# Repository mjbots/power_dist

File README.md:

# mjbots power_dist and mjpower-ss #

This repository contains hardware and firmware for the mjbots
power_dist and mjpower-ss boards.  Both provide pre-charge,
over-current limiting and connector fanout.  The power_dist
additionally provides energy monitoring and a soft-switch
functionality.

# Specifications #

| Name                     | power_dist r4.5b | mjpower-ss r2 |
| ------------------------ |------------------|---------------|
| Voltage Input            | 10-44V           | 10-54V        |
| Current (continous/peak) | 45A/90A          | 45/90A        |
| Output                   | 6x XT30          | 6x XT30       |
| Max load capacitance     | 4000uF           | 4000uF        |
| Quiescent current        | 300uA            | 200uA         |
| Dimensions               | 80x50mm          | 70x50mm       |
| Mass                     | 36g              | 34g           |
| External switch          | X                | X             |
| Soft switch              | X                |               |
| Onboard switch           |                  | X             |
| CAN communication        | X                |               |

# Documentation #

* [Reference](docs/reference.md)

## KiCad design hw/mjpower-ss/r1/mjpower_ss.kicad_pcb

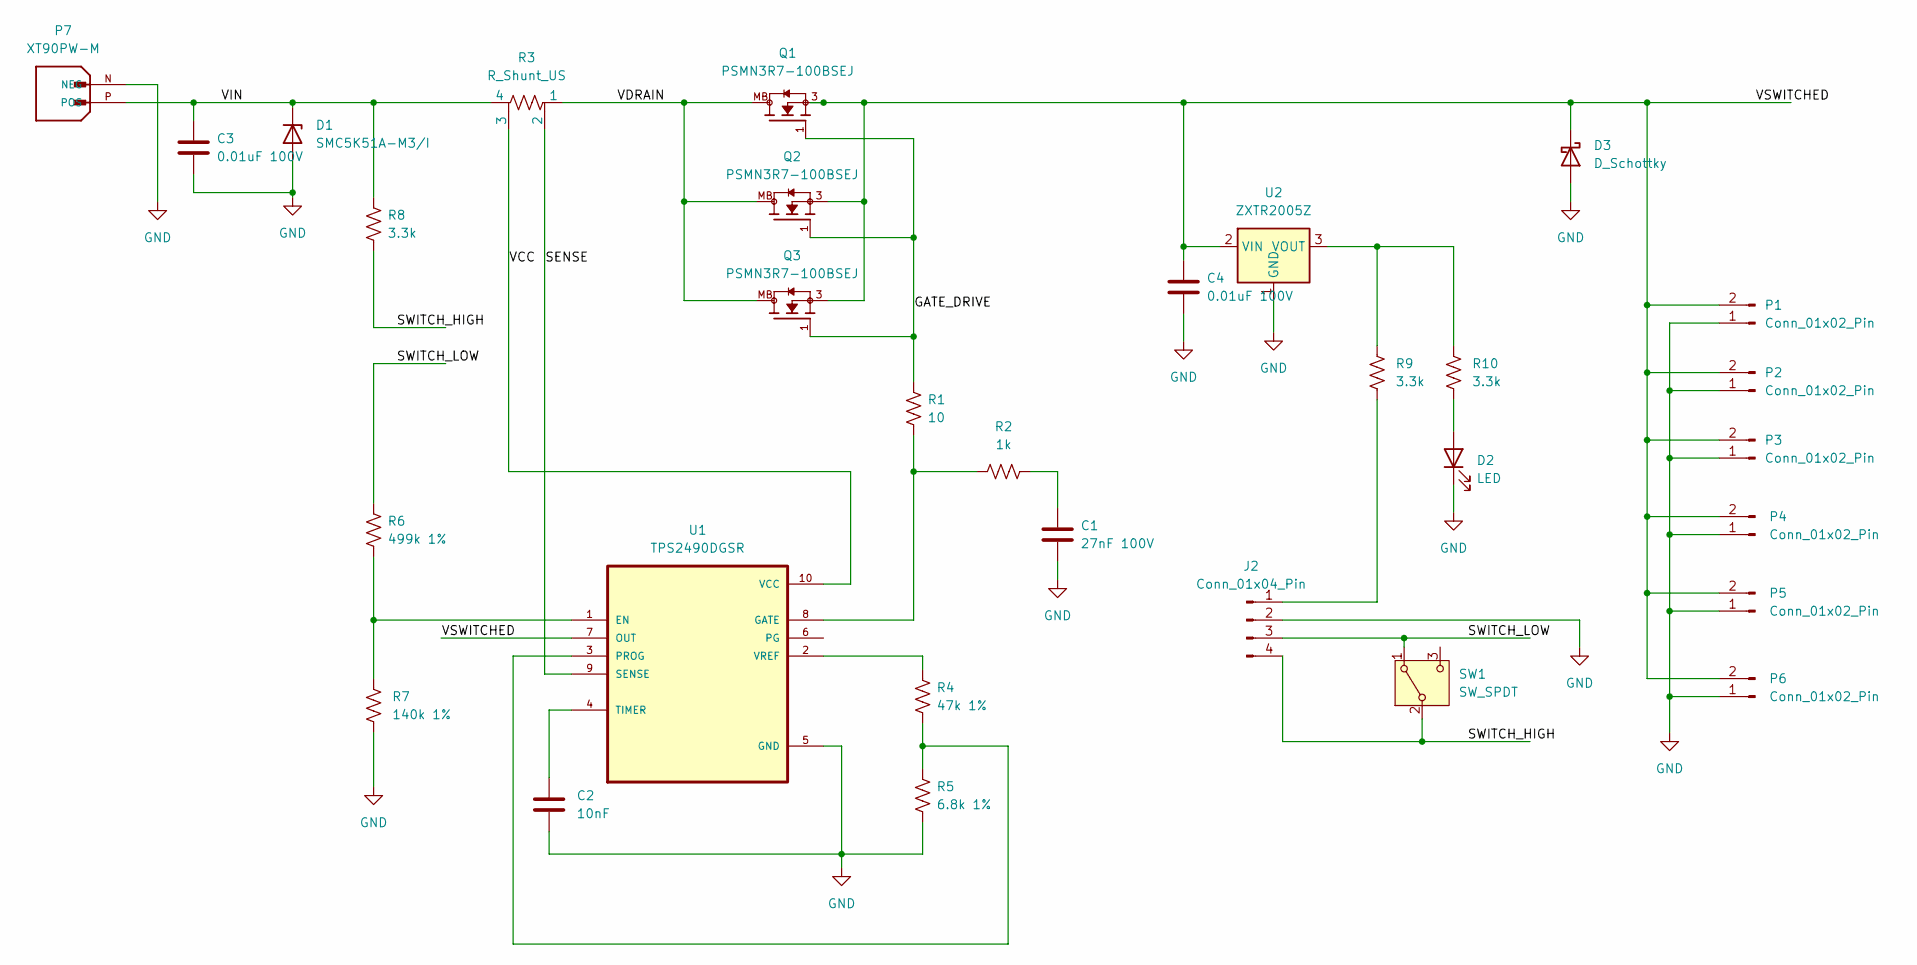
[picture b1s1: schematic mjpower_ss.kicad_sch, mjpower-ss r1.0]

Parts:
C1: 27nF 100V; C_0603_1608Metric; MPN C0603C273K1RACTU
C2: 10nF; C_0603_1608Metric; MPN MF-CAP-0603-0.01uF
C3, C4: 0.01uF 100V; C_0603_1608Metric; MPN GCM188R72A103KA37D
D1: SMC5K51A-M3/I; D_SMC; MPN SMC5K51A-M3/I
D2: LED; LED_1210_3225Metric; MPN APD3224ZGC-F01
D3: D_Schottky; TO-277A; MPN V10P15-M3/H
J2: Conn_01x04_Pin; JST_B4B-PH-SM4-TB; MPN B4B-PH-SM4-TB(LF)(SN)
P1, P2, P3, P4, P5, P6: Conn_01x02_Pin; XT30UPB-F; MPN XT30UPB-F
P7: XT90PW-M; AMASS_XT90PW-M; MPN XT90PW-M
Q1, Q2, Q3: PSMN3R7-100BSEJ; TRANS_PSMN3R7-100BSEJ; MPN PSMN3R7-100BSEJ
R1: 10; R_0603_1608Metric; MPN MF-RES-0603-10
R2: 1k; R_0603_1608Metric; MPN MF-RES-0603-1K
R3: R_Shunt_US; WSL2512_SHUNT; MPN WSLF2512L5000FEA
R4: 47k 1%; R_0603_1608Metric; MPN RC0603FR-0747KL
R5: 6.8k 1%; R_0603_1608Metric; MPN RC0603FR-076K8L
R6: 499k 1%; R_0603_1608Metric; MPN RC0603FR-07499KL
R7: 140k 1%; R_0603_1608Metric; MPN RC0603FR-07140KL
R8, R9, R10: 3.3k; R_0603_1608Metric; MPN RC0603FR-073K3L
SW1: SW_SPDT; SW_G-107-0513; MPN G-107-0513
U1: TPS2490DGSR; SOP50P490X110-10N; MPN TPS2490DGSR
U2: ZXTR2005Z; SOT-89-3; MPN ZXTR2005Z-13

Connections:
/GATE_DRIVE: Q1.1, Q2.1, Q3.1, R1.1
/SENSE: R3.2, U1.9 (SENSE)
/SWITCH_HIGH: J2.4, R8.2, SW1.2 (B)
/SWITCH_LOW: J2.3, R6.1, SW1.1 (A)
/VCC: R3.3, U1.10 (VCC)
/VDRAIN: Q1.MB, Q2.MB, Q3.MB, R3.1
/VIN: C3.1, D1.1 (K), P7.P (POS), R3.4, R8.1
/VSWITCHED: C4.1, D3.1 (K), P1.2, P2.2, P3.2, P4.2, P5.2, P6.2, Q1.3, Q2.3, Q3.3, U1.7 (OUT), U2.2 (VIN)
GND: C1.2, C2.2, C3.2, C4.2, D1.2 (A), D2.1 (K), D3.2 (A), J2.2, P1.1, P2.1, P3.1, P4.1, P5.1, P6.1, P7.N (NEG), R5.2, R7.2, U1.5 (GND), U2.1 (GND)
unnamed: C1.1, R2.2
unnamed: D2.2 (A), R10.1
unnamed: J2.1, R9.1
unnamed: R6.2, R7.1, U1.1 (EN)
unnamed: R1.2, R2.1, U1.8 (GATE)
unnamed: R4.2, R5.1, U1.3 (PROG)
unnamed: C2.1, U1.4 (TIMER)
unnamed: R4.1, U1.2 (VREF)
unnamed: R9.2, R10.2, U2.3 (VOUT)

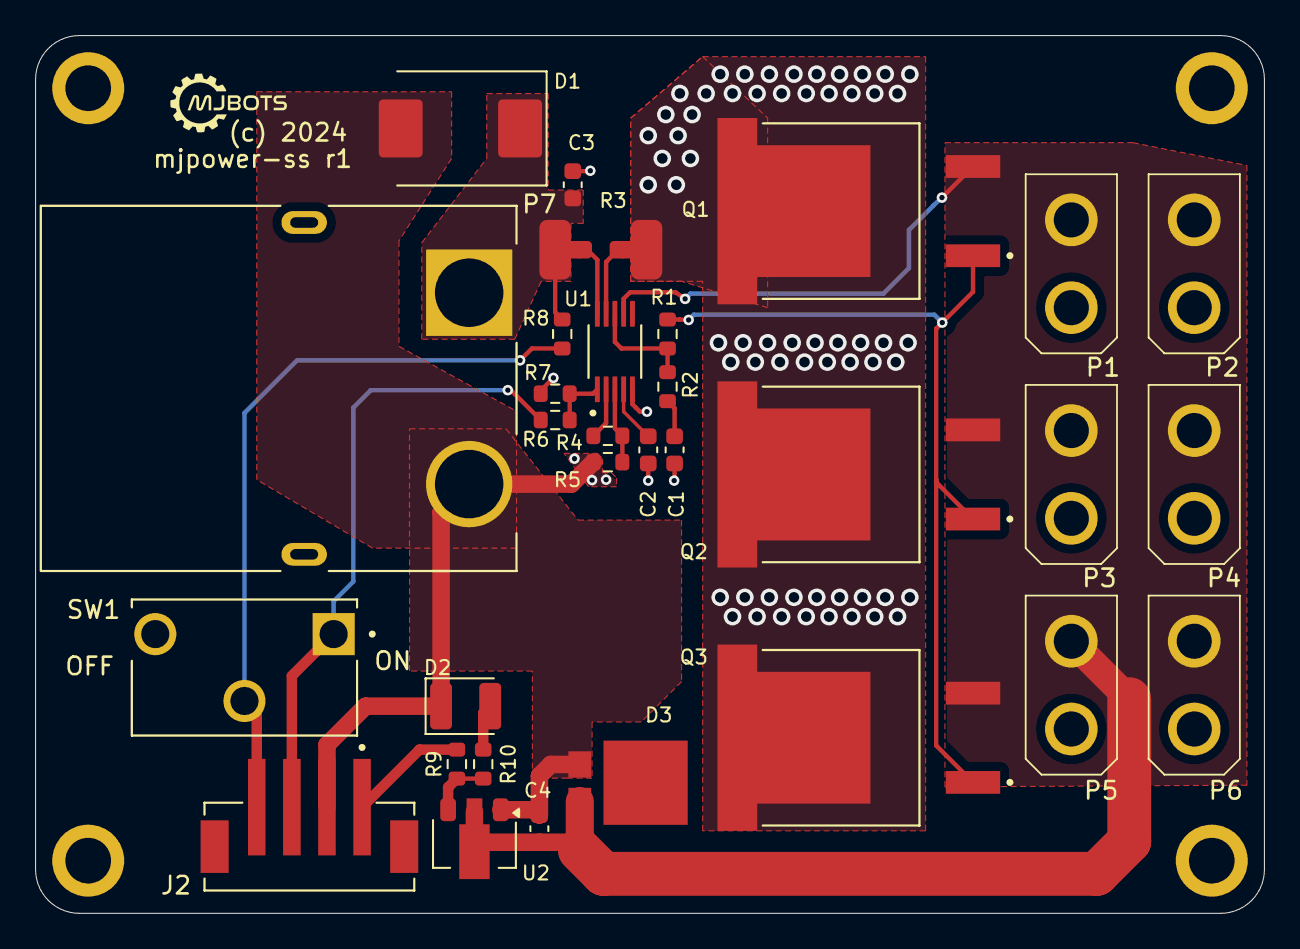
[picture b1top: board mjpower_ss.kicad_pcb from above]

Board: 4 copper layers, 70.0 x 50.0 mm, 31 parts (0 on the bottom side), 18 nets.

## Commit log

2020-12-02 Initial port of sw
2020-12-02 Travis files
2020-12-02 Get license in here
2020-12-02 Hardware designs
2020-12-02 A top level build file
2020-12-07 Work towards functioning r4
    * Beginnings of firmware
    * Initial README and CHANGES
    * Start on r4.1 w/ fixed D3 footprint
2020-12-09 Hack enough stuff in to get tview working
2020-12-09 Fix inconsistency in schematic
2020-12-10 Initial stub of LM5066 support
    This seems to be able to read and report data, and at least input
    voltage seems reasonable.
    tview does seem to become corrupted frequently, possibly related to
    the CAN status spamming.
2020-12-11 Update default bitrate to 1000000
2020-12-11 Calibrate reported current and power
2020-12-12 Document why we configure the lm5066 the way we do
2020-12-12 Fix the git version
    I just neglected to update the namespace in the linkstamp file
2020-12-12 Implement minimal reporting of lm5066 faults
2020-12-12 Turn off retries
2020-12-13 Draft r4.1 based on the LTC4380
2020-12-13 Connect GND/PGND and fix XT90 TH size
2020-12-13 Resize and draft place all silks
2020-12-14 Rename all resistors, capacitors, and diodes
2020-12-14 Fine place silks
2020-12-14 Fix a few minor glitches
2020-12-14 Fix more minor layout and naming glitches
2020-12-14 Add more debugging pads
2020-12-14 More debug pad position tweaks
2020-12-21 r4.1 design files
2020-12-21 Switch to 0.5mohm sense resistor and full voltage range
2020-12-21 Report input voltage over CAN
2020-12-22 Recover from BusOff and once again handle commands
2020-12-23 Capture remaining r4.1 artifacts
2020-12-23 Rough placement of r4.2 with the TPS2490
2020-12-23 r4.2 everything rough routed
2020-12-23 Connect TIMER to an ADC and add a FET temperature sensor
2020-12-23 Renumber all resistors and caps
2020-12-23 Place all silks and add a few more debug points
2021-01-05 Beginnings of making fw work on r4.1
2021-01-05 Get vsamp_in/out working through the opamp buffers
2021-01-05 Get ISAMP_BIAS DAC to work
2021-01-06 Kinda get current sampling to work, although scaling isn't right
2021-01-06 WIP: Attempt unsuccessfully to get current sensing working on r4.1
    This moves the input to PB0 to be buffered by OPAMP3 before being
    amplified by OPAMP6. The amplification appears to be not working, and
    I'm not 100% sure the buffering is working either.
2021-01-07 WIP which actually senses current with amplification
2021-01-08 Finish proving out r4.1 functionality
2021-01-08 Incorporate r4.1 feedback
2021-01-08 Tweak silks and layouts, set isolate for all power nets
2021-01-08 Fine silk placement
2021-01-08 Slight silk tweak
2021-01-10 Capture r4.2 as sent for mf
2021-01-10 Update the solder mask to be more amenable to oshstencil
2021-01-17 Fix a part number
2021-01-19 Minimal updates for r4.2, add decode script
2021-01-20 More work on r4.2 firmware
2021-01-20 Update to r4.3 wiring, add fet temp support
2021-01-20 Start on r4.3
    This version dispenses with all the latching junk for main power, just
    leaving it for the 3.3V rail. Now, the stm32 is completely
    responsible for turning the main power on and off, which could allow
    it to reset the hot swap controller if need be.
2021-01-20 Switch the LTC1787 filter to a 0.1uF
2021-01-22 Updates for r4.3
2021-01-22 Implement an actual state machine and report more values over CAN
2021-01-22 Move some wires further apart
    Reduce the paste fill ratio under the stm32
2021-01-22 Minor position tweaks after gerber viewing
2021-01-24 Capture r4.3
2021-02-13 Add part numbers, rev to 4.3b
2021-03-02 Port reference documentation over
2021-03-02 Increase the pre-charging timeout
2021-03-02 Capture r4.3b
2021-03-02 Remove most firmware support for silk r3.x boards
2021-03-02 Restructure to be slightly more maintainable
    Now we actually have reasonably sized functions, and expose all data
    through a multiplex telemetry protocol. Still necessary are an actual
    register based protocol, and diagnostic mode commands.
2021-03-02 Implement a register based protocol
2021-03-02 Update docs for r4.3b with register based protocol
2021-03-02 Include build timestamp in firmware image
2021-03-02 Default ID to 32
2021-03-02 Add a diagnostic console way to set the switch lock time
2021-03-02 Actually make reading energy via registers work
2021-03-02 Actually obey the lock time!
2021-03-04 Report the serial number over telemetry
2021-04-07 Include mechanical drawings and models for 4.3b
2021-04-19 Document alternate default ID
2021-06-05 Support recording device uuid
2021-06-05 Support 16 bit lock times
2021-06-06 Fix typos in doc
2021-06-06 Update flashing script and documentation
2021-06-06 Improve flashing docs
2022-11-04 Rev to use a staged 5V, then 3.3V regulator
    This way we have a 300mA 5V supply on board to use with a beefier CAN
    transceiver
2022-11-04 Switch to a 5V CAN transceiver
    Add enough 0 ohms and DNPs to support populating with a 3.3V native
    transceiver as well.
2022-11-04 Minor improvements
    * Add a 5V debug pad
    * Tweak routing and silks
2022-11-07 Tweak some silks
2022-11-07 Switch the 27nF cap to one that exists
2022-11-23 Fix TVS diode footprint
2022-12-16 Update bazel_deps
2022-12-16 Enable CAN transceiver delay compensation
2022-12-22 Reroute the regulators and lots of power things
    Try to improve the grounding and decoupling for the buck converters.
    Add some more decoupling caps and place them so as to hopefully reduce
    the amount of ground bounce noise that was interfering with current
    sensing.
2022-12-22 Add a lot more vias
2022-12-23 More tweaks
2022-12-23 Set the ADC prescaler, support r4.5 boards
2022-12-23 Capture r4.4
2022-12-23 More layout and silk tweaks
2022-12-23 Switch PGND to the regulators to be a fill instead of trace
2022-12-23 r4.5 as sent to mfg
2022-12-28 Switch the XT90 drills from 3.7 to 3.9mm
2022-12-31 Final version sent for mf
2023-01-24 Bump version to 4.5b
    Scoot the input regulators around to give the 5V inductor more room
2023-01-24 Improve noise in the power subsystem
    * Replace the 3.3V regulator with a linear one
    * The inductor is just swapped for a shunt, so that the switcher
    could be put back in for testing
    * Increase the 5V regulator input capacitance to 4.7uF from 1uF
    * Shift a bunch of stuff around to make room for the bigger cap
2023-01-24 Connect the grounds on both sides of the 3V regulator
2023-01-27 Attempt to make the isamp capturing be more robust
2023-05-18 * Make the current sense resistor configurable * Provide a diagnostic channel means of forcing the output on/off
2023-05-18 Capture r4.5b
2023-08-17 Update to bazel 5.4.1
    Update deps while we're at it
2023-09-25 Update all copyrights to be mjbots
2024-02-05 Update "most recent" for power_dist documentation
2024-04-03 When we upgraded mjlib, it required a new Poll operation
    Somehow this managed to evade local testing. Without it, the firmware
    does not respond to most, if any, CAN communication.
    Follow up to 4c13a583a957ac7d6b0ae2fe4c5564305a949752
2024-04-03 Provide a configurable mechanism to disable sleeping
2024-05-22 Create two examples showing how to access the power_dist data with python
2024-07-10 Wait a bit before sampling the version pins
2024-07-10 Move all the power_dist board files into their own subdirectory
2024-07-10 Remove legacy board files
2024-09-05 mjpower-ss
    New board, largely same functionality as power_dist.
    + onboard switch
    + smaller size (50x70mm vs 50x80mm)
    + design files in KiCAD
    - CAN-FD monitoring and soft-switch lockout
    Still has:
2024-09-05 Update documentation for mjpower-ss
2025-01-04 Update bazel_deps and mjlib
2025-01-04 Upgrade to bazel 7.4.1
2025-09-29 Support OTP UUID and modern CAN addressing
    This updates power_dist to match moteus in terms of support UUID based
    addressing over CAN. The UUID can now be set in the OTP. UUID
    addressing is supported, and hardware CAN filters are used to only
    receive things that are actually destined for us.
2025-09-29 Add a tool to make release images
2025-11-30 Update mjlib and rules_mbed dependencies
2025-12-01 Fix CAN-FD communication
    Follow up to 8a68840a64530206a1917cc91bbe746aeba026e8
    1. We accidentally turned off delay compensation, which is necessary
    to actually transmit.
    2. Automatic retransmission should be enabled, to match other
    peripheral devices like moteus.
2025-12-16 Update documentation to match actual firmware

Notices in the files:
hw/mjpower-ss/mjpower_ss.kicad_sch:
Licensed under the Apache 2.0 License
hw/mjpower-ss/r1/mjpower_ss.kicad_pcb:
(c) 2024
